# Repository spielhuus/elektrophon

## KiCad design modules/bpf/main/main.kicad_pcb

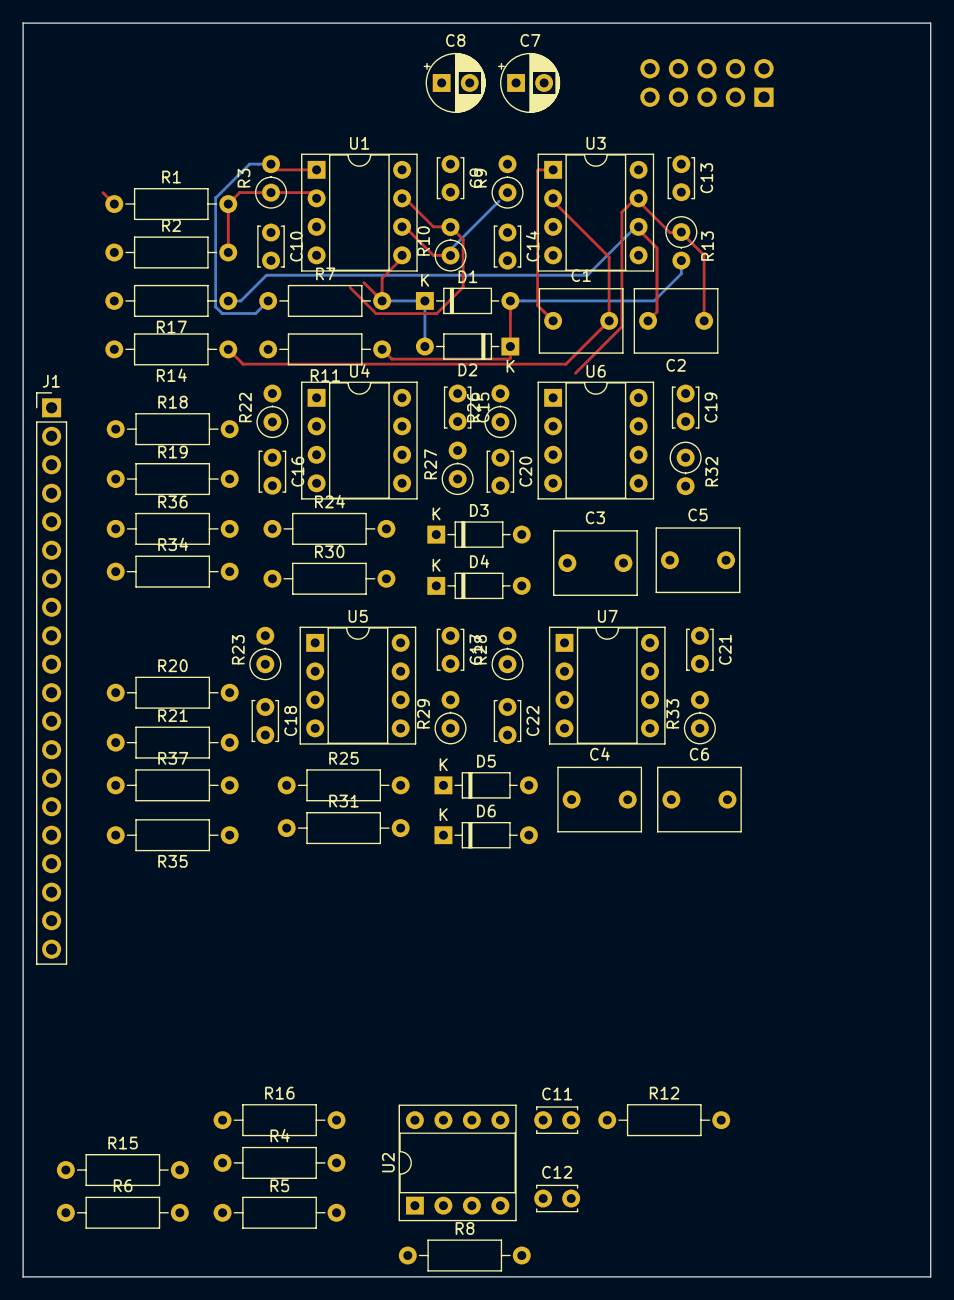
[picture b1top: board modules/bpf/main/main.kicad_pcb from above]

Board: 2 copper layers, 80.9 x 111.8 mm, 74 parts (1 on the bottom side), 49 nets.

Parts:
C1, C2, C3, C4, C5, C6: 22n; C_Rect_L7.2mm_W5.5mm_P5.00mm_FKS2_FKP2_MKS2_MKP2
C7, C8: 10u; CP_Radial_D5.0mm_P2.50mm
C9, C10, C11, C12, C13, C14, C15, C16, C17, C18, C19, C20, C21, C22: 0.1u; C_Disc_D3.4mm_W2.1mm_P2.50mm
D1, D2, D3, D4, D5, D6: 1N4148; D_DO-35_SOD27_P7.62mm_Horizontal
J1: Conn_01x20_Female; PinHeader_1x20_P2.54mm_Vertical
J2: IDC Header; IDC-Header_2x05_P2.54mm_Vertical
R1, R2, R18, R19, R20, R21: 47k; R_Axial_DIN0207_L6.3mm_D2.5mm_P10.16mm_Horizontal
R3, R22, R23: 47k; R_Axial_DIN0207_L6.3mm_D2.5mm_P2.54mm_Vertical
R4, R5, R6, R8, R12, R15, R16: 100k; R_Axial_DIN0207_L6.3mm_D2.5mm_P10.16mm_Horizontal
R7, R24, R25: 10k; R_Axial_DIN0207_L6.3mm_D2.5mm_P10.16mm_Horizontal
R9, R10, R26, R27, R28, R29: 10k; R_Axial_DIN0207_L6.3mm_D2.5mm_P2.54mm_Vertical
R11, R30, R31: 15k; R_Axial_DIN0207_L6.3mm_D2.5mm_P10.16mm_Horizontal
R13, R32, R33: 6k8; R_Axial_DIN0207_L6.3mm_D2.5mm_P2.54mm_Vertical
R14, R17, R34, R35, R36, R37: 680; R_Axial_DIN0207_L6.3mm_D2.5mm_P10.16mm_Horizontal
U1, U2, U3, U4, U5, U6, U7: TL072; DIP-8_W7.62mm_Socket

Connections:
+5V: J2.9, J2.10
+15V: C7.1, C9.1, C11.1, C13.1, C15.1, C17.1, C19.1, C21.1, J2.3, J2.4, U1.8, U2.8, U3.8, U4.8, U5.8, U6.8, U7.8
-15V: C8.2, C10.2, C12.2, C14.2, C16.2, C18.2, C20.2, C22.2, J2.1, J2.2, U1.4, U2.4, U3.4, U4.4, U5.4, U6.4, U7.4
FREQ_1_a: J1.4, R10.2, U1.7
FREQ_1_b: J1.5, R17.2
FREQ_1_c: J1.6, R14.2
FREQ_2_a: J1.10, R27.2, U4.7
FREQ_2_b: J1.11, R36.2
FREQ_2_c: J1.12, R34.2
FREQ_3_a: J1.16, R29.2, U5.7
FREQ_3_b: J1.17, R37.2
FREQ_3_c: J1.18, R35.2
GND: C7.2, C8.1, C9.2, C10.1, C11.2, C12.1, C13.2, C14.1, C15.2, C16.1, C17.2, C18.1, C19.2, C20.1, C21.2, C22.1, J2.5, J2.6, J2.7, J2.8, R11.2, R30.2, R31.2, U1.3, U2.3, U2.5, U3.3, U3.5, U4.3, U5.3, U6.3, U6.5, U7.3, U7.5
IN: J1.1, R1.1, R18.1, R20.1
IN_1: J1.2, R2.1
IN_2: J1.8, R19.1
IN_3: J1.14, R21.1
unnamed: C1.1, R9.2, U3.1
unnamed: C1.2, R14.1, U3.2
unnamed: C2.2, R17.1, U3.6
unnamed: C3.1, R26.2, U6.1
unnamed: C3.2, R34.1, U6.2
unnamed: C4.1, R28.2, U7.1
unnamed: C4.2, R35.1, U7.2
unnamed: C5.2, R36.1, U6.6
unnamed: C6.2, R37.1, U7.6
unnamed: D1.2, D2.1, R11.1, R13.2
unnamed: D3.2, D4.1, R30.1, R32.2
unnamed: D5.2, D6.1, R31.1, R33.2
unnamed: R1.2, R2.2, R3.1, U1.2
unnamed: R3.2, R7.1, U1.1
unnamed: R4.1, R5.1, R6.1, R8.2, U2.2
unnamed: R9.1, R10.1, U1.6
unnamed: R12.1, R15.2, U2.6
unnamed: R8.1, R12.2, U2.1
unnamed: R16.2, U2.7
unnamed: R18.2, R19.2, R22.1, U4.2
unnamed: R20.2, R21.2, R23.1, U5.2
unnamed: R22.2, R24.1, U4.1
unnamed: R23.2, R25.1, U5.1
unnamed: R26.1, R27.1, U4.6
unnamed: R28.1, R29.1, U5.6
OUT: J1.20, R15.1, R16.1
OUT_1: C2.1, J1.7, R13.1, U3.7
OUT_2: C5.1, J1.13, R32.1, U6.7
OUT_3: C6.1, J1.19, R33.1, U7.7
RES_1: D1.1, D2.2, J1.3, R7.2, U1.5
RES_2: D3.1, D4.2, J1.9, R24.2, U4.5
RES_3: D5.1, D6.2, J1.15, R25.2, U5.5

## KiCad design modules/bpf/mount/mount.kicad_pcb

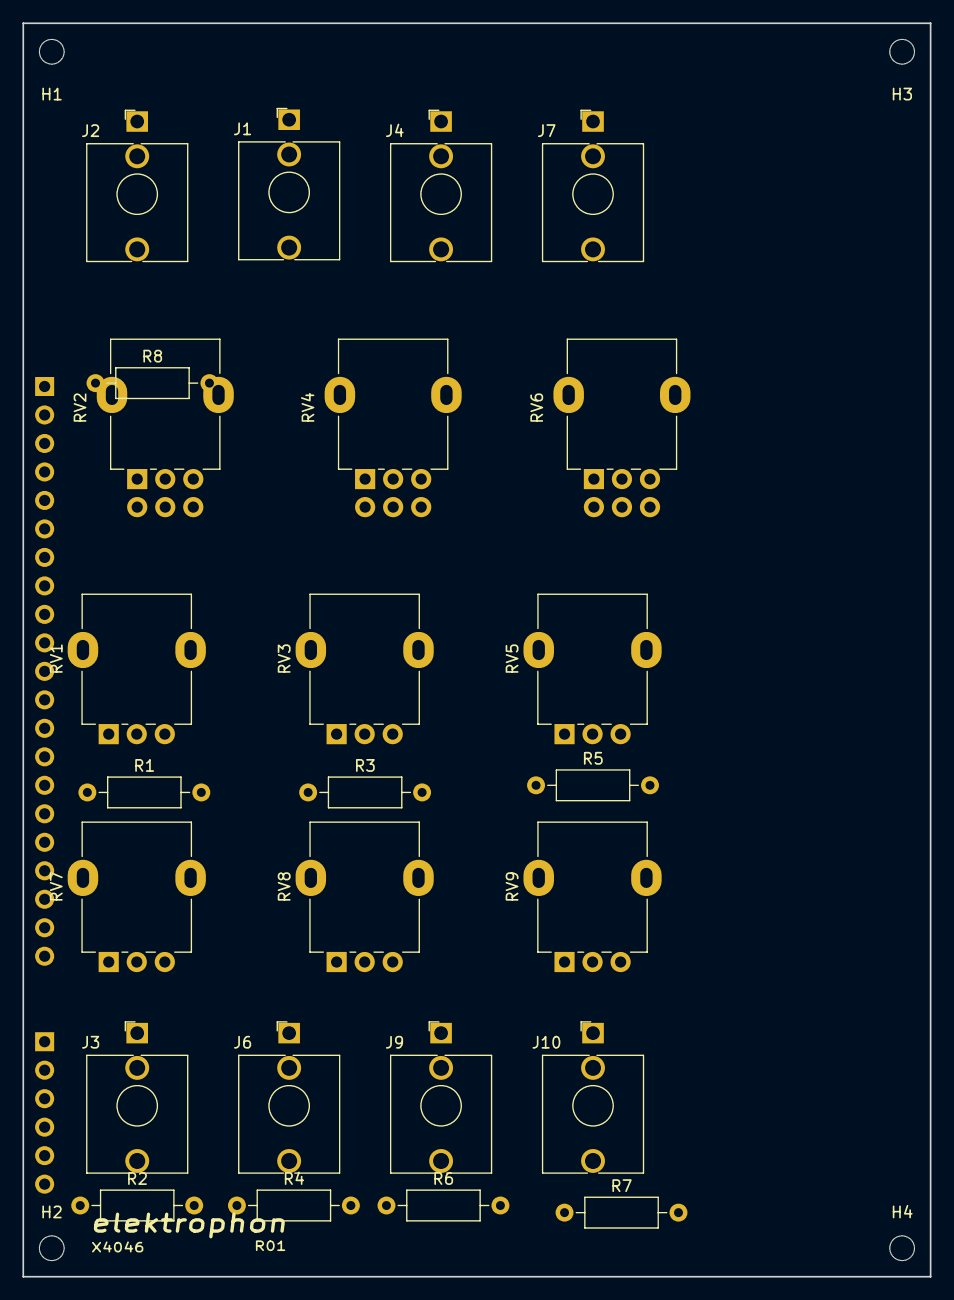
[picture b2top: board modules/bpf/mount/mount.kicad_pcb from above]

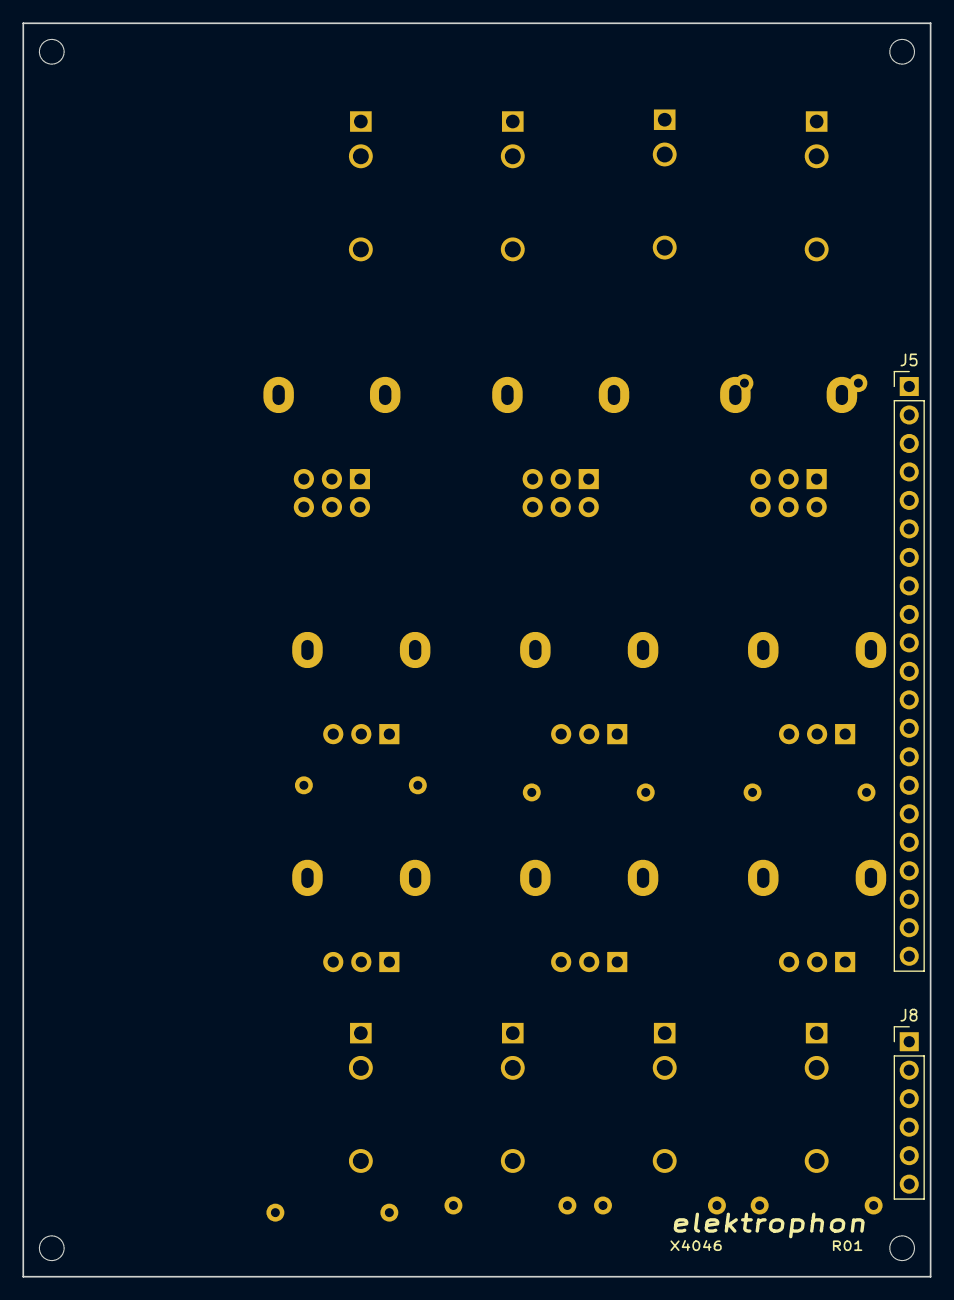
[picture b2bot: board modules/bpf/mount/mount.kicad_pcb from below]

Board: 2 copper layers, 80.9 x 111.8 mm, 31 parts (2 on the bottom side), 35 nets, no tracks yet.

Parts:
H1, H2, H3, H4: MountingHole; MountingHole_2.2mm_M2
J1, J2, J3, J4, J6, J7, J9, J10: AudioJack2_SwitchT; Jack_3.5mm_WQP-PJ398SM_Vertical
J5: Conn_01x21_Male; PinHeader_1x21_P2.54mm_Vertical
J8: Conn_01x06_Male; PinHeader_1x06_P2.54mm_Vertical
R1, R3, R5: 4k7; R_Axial_DIN0207_L6.3mm_D2.5mm_P10.16mm_Horizontal
R2, R4, R6, R7: 1k; R_Axial_DIN0207_L6.3mm_D2.5mm_P10.16mm_Horizontal
R8: 22k; R_Axial_DIN0207_L6.3mm_D2.5mm_P10.16mm_Horizontal
RV1, RV3, RV5: 50k; Potentiometer_Alpha_RD901F-40-00D_Single_Vertical
RV2, RV4, RV6: 100k; Potentiometer_Alpha_RD902F-40-00D_Dual_Vertical
RV7, RV8, RV9: 100k; Potentiometer_Alpha_RD901F-40-00D_Single_Vertical

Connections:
FREQ_1_a: J5.5, RV2.1
FREQ_1_b: J5.6, RV2.2, RV2.3
FREQ_1_c: J5.7, RV2.4
FREQ_2_a: J5.11, RV4.1
FREQ_2_b: J5.12, RV4.2, RV4.3
FREQ_2_c: J5.13, RV4.4
FREQ_3_a: J5.17, RV6.1
FREQ_3_b: J5.18, RV6.2, RV6.3
FREQ_3_c: J5.19, RV6.4
GND: J1.S, J2.S, J3.S, J4.S, J5.1, J6.S, J7.S, J9.S, J10.S, R1.2, R3.2, R5.2, RV7.1, RV8.1, RV9.1
IN: J2.T, J5.2
IN_1: J1.T, J5.3
IN_2: J4.T, J5.9
IN_3: J5.15, J7.T
MIX_1_a: J8.1, RV7.3
MIX_1_b: J8.2, RV7.2
MIX_2_a: J8.3, RV8.3
MIX_2_b: J8.4, RV8.2
MIX_3_a: J8.5, RV9.3
MIX_3_b: J8.6, RV9.2
unnamed: J3.T, R2.2
unnamed: J6.T, R4.2
unnamed: J9.T, R6.2
unnamed: J10.T, R7.2
unnamed: R1.1, RV1.1
unnamed: R3.1, RV3.1
unnamed: R5.1, RV5.1
unnamed: R8.1, RV1.3
OUT: J5.21, R7.1
OUT_1: J5.8, R2.1, R8.2, RV2.5, RV2.6
OUT_2: J5.14, R4.1, RV3.3, RV4.5, RV4.6
OUT_3: J5.20, R6.1, RV5.3, RV6.5, RV6.6
RES_1: J5.4, RV1.2
RES_2: J5.10, RV3.2
RES_3: J5.16, RV5.2

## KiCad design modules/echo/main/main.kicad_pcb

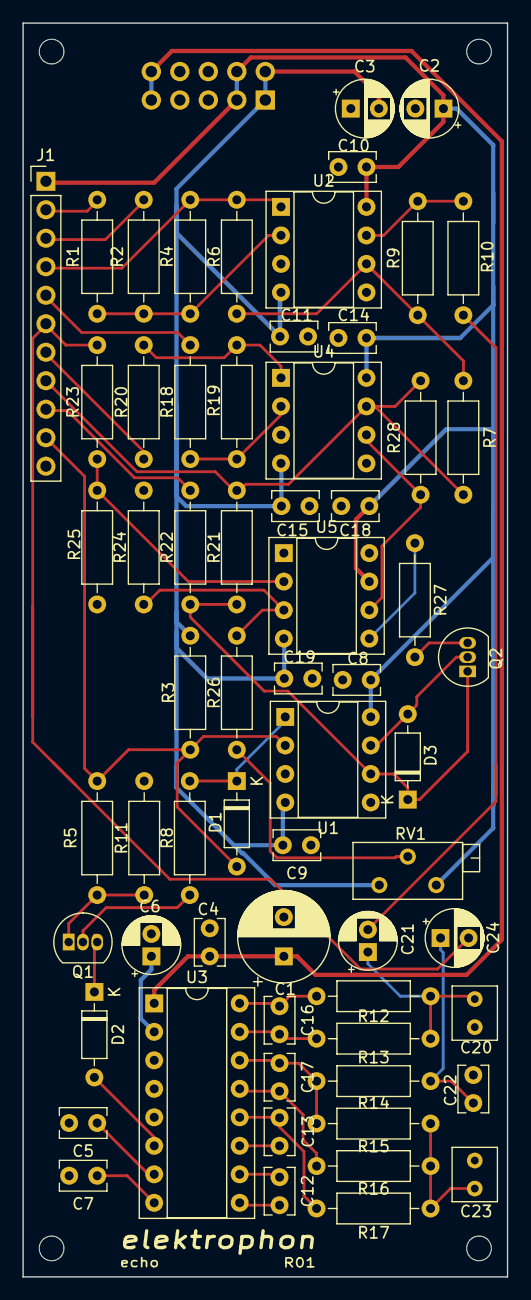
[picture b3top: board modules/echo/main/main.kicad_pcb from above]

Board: 2 copper layers, 43.2 x 111.8 mm, 69 parts (1 on the bottom side), 46 nets.

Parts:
C1: 100u; CP_Radial_D8.0mm_P3.50mm
C2, C3, C24: 10u; CP_Radial_D5.0mm_P2.50mm
C4, C5, C7, C8, C9, C10, C11, C12, C13, C14, C15, C18, C19: 0.1u; C_Rect_L4.0mm_W2.5mm_P2.50mm
C6, C21: 4.7u; CP_Radial_D5.0mm_P2.00mm
C16, C17: 560p; C_Rect_L4.0mm_W2.5mm_P2.50mm
C20, C23: 5n6; C_Rect_L4.6mm_W3.8mm_P2.50mm_MKS02_FKP02
C22: 10n; C_Rect_L4.0mm_W2.5mm_P2.50mm
D1, D2, D3: 1N4148; D_DO-35_SOD27_P7.62mm_Horizontal
H1, H2, H3, H4: MountingHole; MountingHole_2.2mm_M2
J1: Conn_01x11_Female; PinHeader_1x11_P2.54mm_Vertical
J2: IDC Header; IDC-Header_2x05_P2.54mm_Vertical
Q1: 2N3904; TO-92_Inline
Q2: 2N3906; TO-92_Inline
R1, R2, R4, R6, R7, R9, R18, R19, R23: 100k; R_Axial_DIN0207_L6.3mm_D2.5mm_P10.16mm_Horizontal
R3: 300k; R_Axial_DIN0207_L6.3mm_D2.5mm_P10.16mm_Horizontal
R5, R27: 27k; R_Axial_DIN0207_L6.3mm_D2.5mm_P10.16mm_Horizontal
R8: 220k; R_Axial_DIN0207_L6.3mm_D2.5mm_P10.16mm_Horizontal
R10, R13, R15, R17: 15k; R_Axial_DIN0207_L6.3mm_D2.5mm_P10.16mm_Horizontal
R11, R24, R25: 470; R_Axial_DIN0207_L6.3mm_D2.5mm_P10.16mm_Horizontal
R12, R16: 10k; R_Axial_DIN0207_L6.3mm_D2.5mm_P10.16mm_Horizontal
R14: 2k7; R_Axial_DIN0207_L6.3mm_D2.5mm_P10.16mm_Horizontal
R20: 1k; R_Axial_DIN0207_L6.3mm_D2.5mm_P10.16mm_Horizontal
R21: 20k; R_Axial_DIN0207_L6.3mm_D2.5mm_P10.16mm_Horizontal
R22, R28: 47k; R_Axial_DIN0207_L6.3mm_D2.5mm_P10.16mm_Horizontal
R26: 1M; R_Axial_DIN0207_L6.3mm_D2.5mm_P10.16mm_Horizontal
RV1: 100k; Potentiometer_Bourns_3296Z_Horizontal
U1: TL072; DIP-8_W7.62mm_Socket
U2, U4: OPA2134; DIP-8_W7.62mm_Socket
U3: PT2399; DIP-16_W7.62mm_Socket
U5: CA3080; DIP-8_W7.62mm_Socket

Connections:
+5V: C1.1, C4.1, J2.9, J2.10, U3.1
+15V: C2.1, C8.1, C10.1, C14.1, C18.1, J1.1, J2.3, J2.4, RV1.3, U1.8, U2.8, U4.8, U5.7
-15V: C3.2, C9.2, C11.2, C15.2, C19.2, J2.1, J2.2, R3.1, RV1.1, U1.4, U2.4, U4.4, U5.4
/CV: D1.2, J1.10, R3.2, R5.2, U1.2
/IN1: J1.2, R1.2
/IN2: J1.3, R2.2
/MIXED_OUT: J1.7, R20.1
/MIX_1: J1.4, R4.1, R6.2, U2.1
/MIX_2: J1.5, R18.2
/MIX_3: C24.2, J1.6, R23.2
/RECIRC: J1.8, R7.2, R21.2, R28.2, U4.7
/RECIRC_ATTEN: J1.9, R22.2
/VCO: D2.2, U3.6
GND: C1.2, C2.2, C3.1, C4.2, C5.2, C6.2, C7.2, C8.2, C9.1, C10.2, C11.1, C14.2, C15.1, C18.2, C19.1, C20.2, C22.2, C23.2, J1.11, J2.5, J2.6, J2.7, J2.8, R11.1, R24.2, R25.2, U1.3, U1.5, U2.3, U2.5, U3.3, U3.4, U4.3, U4.5
unnamed: C5.1, U3.7
unnamed: C6.1, U3.2
unnamed: C7.1, U3.8
unnamed: C12.1, U3.10
unnamed: C12.2, U3.9
unnamed: C13.1, U3.11
unnamed: C13.2, R17.2, U3.12
unnamed: C16.1, R12.2, U3.16
unnamed: C16.2, R13.2, U3.15
unnamed: C17.1, R14.2, R15.2, U3.14
unnamed: C17.2, R16.2, U3.13
unnamed: C20.1, C21.1, R12.1, R13.1
unnamed: C21.2, R10.1
unnamed: C22.1, C24.1, R14.1
unnamed: C23.1, R15.1, R16.1, R17.1
unnamed: D1.1, R8.2, U1.1
unnamed: D2.1, Q1.3
unnamed: D3.1, Q2.1, R21.1, R22.1, U1.6
unnamed: D3.2, Q2.2, U1.7
unnamed: Q1.1, R5.1, R11.2
unnamed: Q1.2, R8.1
unnamed: Q2.3, R27.1
unnamed: R1.1, R2.1, R4.2, U2.2
unnamed: R6.1, R7.1, R9.2, U2.6
unnamed: R9.1, R10.2, U2.7
unnamed: R18.1, R19.2, U4.2
unnamed: R19.1, R20.2, U4.1
unnamed: R23.1, R25.1, U5.2
unnamed: R24.1, R26.2, U5.3
unnamed: R26.1, RV1.2
unnamed: R27.2, U5.5
unnamed: R28.1, U4.6, U5.6

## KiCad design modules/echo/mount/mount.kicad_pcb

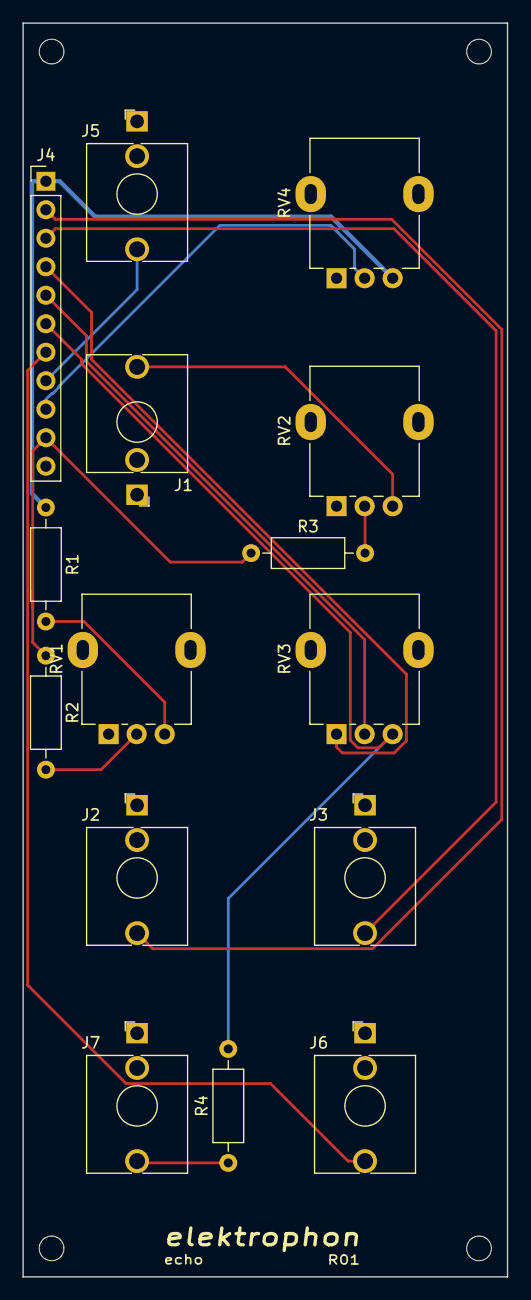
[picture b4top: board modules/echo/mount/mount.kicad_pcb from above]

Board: 2 copper layers, 43.2 x 111.8 mm, 19 parts (0 on the bottom side), 16 nets.

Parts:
H1, H2, H3, H4: MountingHole; MountingHole_2.2mm_M2
J1: CV; Jack_3.5mm_WQP-PJ398SM_Vertical
J2, J3: IN; Jack_3.5mm_WQP-PJ398SM_Vertical
J4: Conn_01x11_Male; PinHeader_1x11_P2.54mm_Vertical
J5: RECIRC; Jack_3.5mm_WQP-PJ398SM_Vertical
J6: Mixed OUT; Jack_3.5mm_WQP-PJ398SM_Vertical
J7: delayed OUT; Jack_3.5mm_WQP-PJ398SM_Vertical
R1: 360; R_Axial_DIN0207_L6.3mm_D2.5mm_P10.16mm_Horizontal
R2: 300k; R_Axial_DIN0207_L6.3mm_D2.5mm_P10.16mm_Horizontal
R3: 100k; R_Axial_DIN0207_L6.3mm_D2.5mm_P10.16mm_Horizontal
R4: 1k; R_Axial_DIN0207_L6.3mm_D2.5mm_P10.16mm_Horizontal
RV1: 100k; Potentiometer_Alpha_RD901F-40-00D_Single_Vertical
RV2, RV4: 10k; Potentiometer_Alpha_RD901F-40-00D_Single_Vertical
RV3: 10k LIN; Potentiometer_Alpha_RD901F-40-00D_Single_Vertical

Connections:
+15V: J4.1, R1.1, RV4.3
/CV: J4.10, R2.1, R3.1
/IN1: J2.T, J4.2
/IN2: J3.T, J4.3
/MIXED_OUT: J4.7, J6.T
/MIX_1: J4.4, RV3.1
/MIX_2: J4.5, RV3.2
/MIX_3: J4.6, R4.2, RV3.3
/RECIRC_ATTEN: J4.9, RV4.2
/RECIRC_CV: J4.8, J5.T
GND: J1.S, J2.S, J3.S, J4.11, J5.S, J6.S, J7.S, RV1.1, RV2.1, RV4.1
unnamed: J1.T, RV2.3
unnamed: J7.T, R4.1
unnamed: R1.2, RV1.3
unnamed: R2.2, RV1.2
unnamed: R3.2, RV2.2

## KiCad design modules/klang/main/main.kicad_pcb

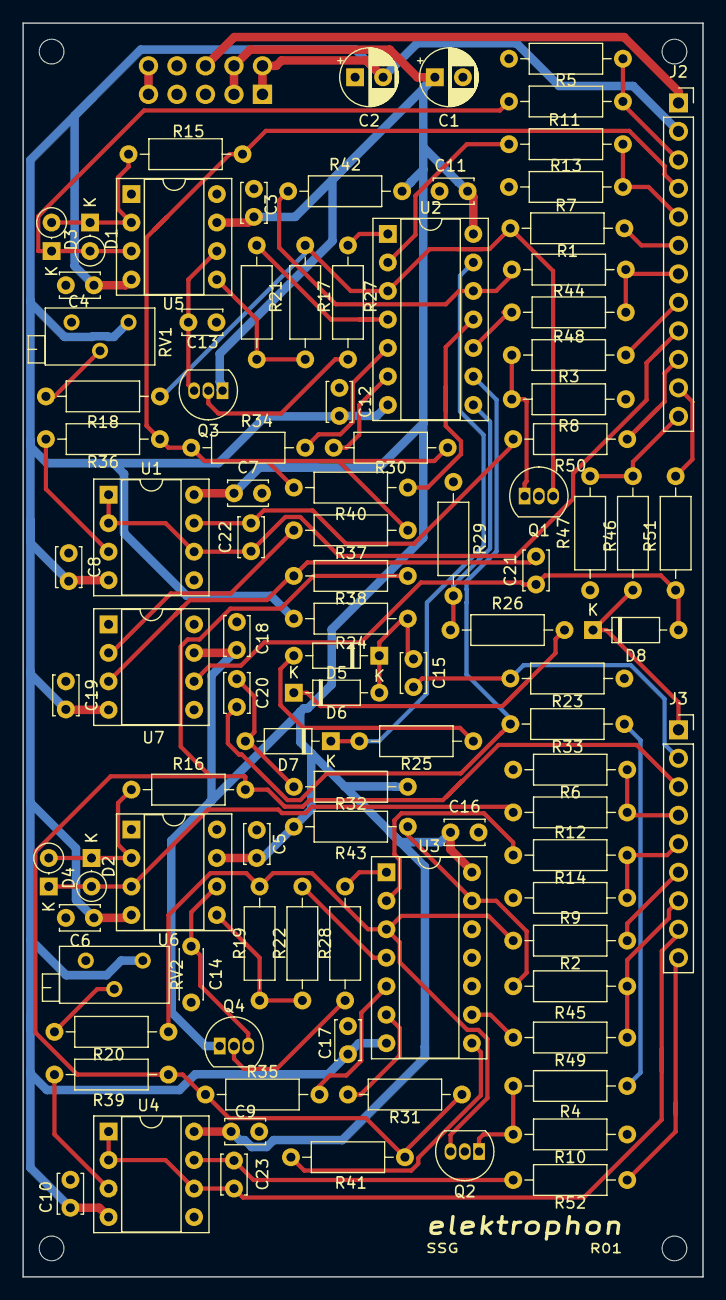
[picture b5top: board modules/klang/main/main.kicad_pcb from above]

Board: 2 copper layers, 60.6 x 111.8 mm, 99 parts (1 on the bottom side), 70 nets.

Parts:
C1, C2: 10u; CP_Radial_D5.0mm_P2.50mm
C3, C4, C5, C6, C7, C8, C9, C10, C11, C12, C16, C17, C18, C19: 0.1u; C_Disc_D3.4mm_W2.1mm_P2.50mm
C13: 100n; C_Disc_D3.4mm_W2.1mm_P2.50mm
C14: 220n; C_Disc_D4.3mm_W1.9mm_P5.00mm
C15, C20: 1n; C_Disc_D3.4mm_W2.1mm_P2.50mm
C21: 100p; C_Disc_D3.4mm_W2.1mm_P2.50mm
C22, C23: 47p; C_Disc_D3.4mm_W2.1mm_P2.50mm
D1, D2, D3, D4: 1N4148; D_DO-35_SOD27_P2.54mm_Vertical_KathodeUp
D5, D6, D7, D8: 1N4148; D_DO-35_SOD27_P7.62mm_Horizontal
J1: IDC Header; IDC-Header_2x05_P2.54mm_Vertical
J2: Conn_01x12_Female; PinSocket_1x12_P2.54mm_Vertical
J3: Conn_01x09_Female; PinSocket_1x09_P2.54mm_Vertical
Q1, Q2: PN4250; TO-92_Inline
Q3, Q4: 2N5457; TO-92_Inline
R1, R2, R13, R14: 2M7; R_Axial_DIN0207_L6.3mm_D2.5mm_P10.16mm_Horizontal
R3, R4, R5, R6, R11, R12, R15, R16, R24: 33k; R_Axial_DIN0207_L6.3mm_D2.5mm_P10.16mm_Horizontal
R7, R9, R23, R26: 100k; R_Axial_DIN0207_L6.3mm_D2.5mm_P10.16mm_Horizontal
R8, R10, R21, R22: 15k; R_Axial_DIN0207_L6.3mm_D2.5mm_P10.16mm_Horizontal
R17, R19: 82k; R_Axial_DIN0207_L6.3mm_D2.5mm_P10.16mm_Horizontal
R18, R20, R32: 1M5; R_Axial_DIN0207_L6.3mm_D2.5mm_P10.16mm_Horizontal
R25: 680k; R_Axial_DIN0207_L6.3mm_D2.5mm_P10.16mm_Horizontal
R27, R31: 820k; R_Axial_DIN0207_L6.3mm_D2.5mm_P10.16mm_Horizontal
R28: 1m; R_Axial_DIN0207_L6.3mm_D2.5mm_P10.16mm_Horizontal
R29: 4M7; R_Axial_DIN0207_L6.3mm_D2.5mm_P10.16mm_Horizontal
R30, R42, R43: 1M; R_Axial_DIN0207_L6.3mm_D2.5mm_P10.16mm_Horizontal
R33, R34, R35: 330; R_Axial_DIN0207_L6.3mm_D2.5mm_P10.16mm_Horizontal
R36, R37, R38, R39: 10k; R_Axial_DIN0207_L6.3mm_D2.5mm_P10.16mm_Horizontal
R40, R41: 470k; R_Axial_DIN0207_L6.3mm_D2.5mm_P10.16mm_Horizontal
R44, R45: 2M2; R_Axial_DIN0207_L6.3mm_D2.5mm_P10.16mm_Horizontal
R46, R47, R48, R49, R51: 3k3; R_Axial_DIN0207_L6.3mm_D2.5mm_P10.16mm_Horizontal
R50, R52: 100; R_Axial_DIN0207_L6.3mm_D2.5mm_P10.16mm_Horizontal
RV1, RV2: 25k; Potentiometer_Bourns_3296Z_Horizontal
U1, U4: TL072; DIP-8_W7.62mm_Socket
U2, U3: LM3900; DIP-14_W7.62mm_Socket
U5, U6: CA3080; DIP-8_W7.62mm_Socket
U7: LM741; DIP-8_W7.62mm_Socket

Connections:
+5V: J1.9, J1.10
+15V: C1.1, C3.1, C5.1, C7.1, C9.1, C11.1, C16.1, C18.1, J1.3, J1.4, Q3.1, Q4.1, R32.2, R42.2, R43.2, U1.8, U2.14, U3.14, U4.8, U5.7, U6.7, U7.7
-15V: C2.2, C4.2, C6.2, C8.2, C10.2, C12.2, C17.2, C19.2, J1.1, J1.2, J2.2, R24.1, RV1.1, RV2.1, U1.4, U2.7, U3.7, U4.4, U5.4, U6.4, U7.4
/HOLD: R4.2, R33.1
COUPLER_5V: J2.12, R46.1, R47.2
COUPLER_HOT: J2.11, R51.1
CYCLE_1: J2.7, R44.1, R48.1
CYCLE_2: J3.7, R45.1, R49.1
GND: C1.2, C2.1, C3.2, C4.1, C5.2, C6.1, C7.2, C8.1, C9.2, C10.1, C11.2, C12.1, C13.2, C14.2, C16.2, C17.1, C18.2, C19.1, J1.5, J1.6, J1.7, J1.8, J2.1, Q1.2, Q2.2, R5.1, R6.1, R7.1, R8.1, R9.1, R10.1, R23.1, R29.1, R47.1, RV1.3, RV2.3, U1.5, U4.5
HOLD_1: J2.8, R3.2
IN_1: J2.3, R5.2, R11.2
IN_2: J3.4, R6.2, R12.2
LED: D8.1, J3.1, R46.2
LED_1_a: C22.1, J2.9, U1.1, U1.2, U1.6
LED_1_b: J2.10, R50.1
LED_2_a: C23.1, J3.8, U4.1, U4.2, U4.6
LED_2_b: J3.9, R52.1
unnamed: C13.1, Q3.3, U5.6
unnamed: C14.1, Q4.3, U6.6
unnamed: C15.2, D5.1, D6.2, R24.2
unnamed: C20.1, R33.2, U2.9
unnamed: C20.2, D7.2, R32.1
unnamed: C21.1, D8.2, R51.2, U7.6
unnamed: C21.2, R38.1, U7.3
unnamed: C22.2, R50.2, U1.7
unnamed: C23.2, R52.2, U4.7
unnamed: D1.1, D3.2, R15.2, U5.2
unnamed: D1.2, D3.1, R11.1, U5.3
unnamed: D2.1, D4.2, R16.2, U6.2
unnamed: D2.2, D4.1, R12.1, U6.3
unnamed: D5.2, R25.2
unnamed: D6.1, R26.2
unnamed: D7.1, R25.1, U2.13
unnamed: Q1.1, R3.1, R8.2
unnamed: Q1.3, R1.1, R17.2, R18.2, U2.3
unnamed: Q2.1, R4.1, R10.2
unnamed: Q2.3, R2.1, R19.2, R20.2, U3.3
unnamed: Q3.2, R27.2
unnamed: Q4.2, R28.2
unnamed: R13.1, U2.2
unnamed: R14.1, U3.2
unnamed: R17.1, R21.1, U5.5
unnamed: R18.1, RV1.2
unnamed: R19.1, R22.1, U6.5
unnamed: R20.1, RV2.2
unnamed: R21.2, U2.4
unnamed: R22.2, U3.4
unnamed: R26.1, R29.2, U2.8
unnamed: R27.1, U2.1
unnamed: R28.1, U3.1
unnamed: R30.1, U2.6
unnamed: R31.1, U3.6
unnamed: R34.2, U2.5
unnamed: R35.2, U3.5
unnamed: R36.1, U1.3
unnamed: R37.1, U7.2
unnamed: R39.1, U4.3
unnamed: R40.1, U2.11
unnamed: R41.1, U3.8
unnamed: R42.1, R44.2, U2.12
unnamed: R43.1, R45.2, U3.13
unnamed: R48.2, U2.10
unnamed: R49.2, U3.9
OUT_1: J2.4, R15.1, R30.2, R34.1, R36.2, R37.2, R40.2
OUT_2: J3.3, R16.1, R31.2, R35.1, R38.2, R39.2, R41.2
RATE_1: J2.6, R1.2
RATE_2: J3.6, R2.2
SAMPLE_2: C15.1, J3.2, R23.2
VC_1: J2.5, R7.2, R13.2
VC_2: J3.5, R9.2, R14.2

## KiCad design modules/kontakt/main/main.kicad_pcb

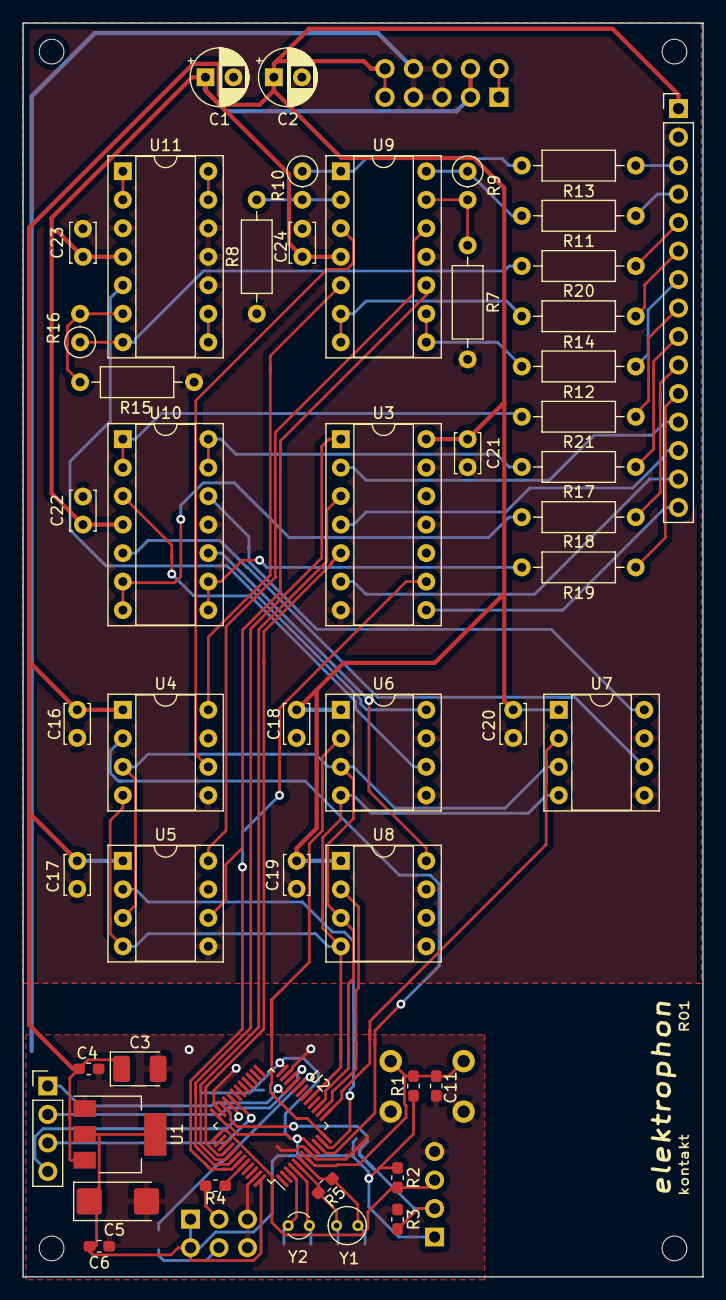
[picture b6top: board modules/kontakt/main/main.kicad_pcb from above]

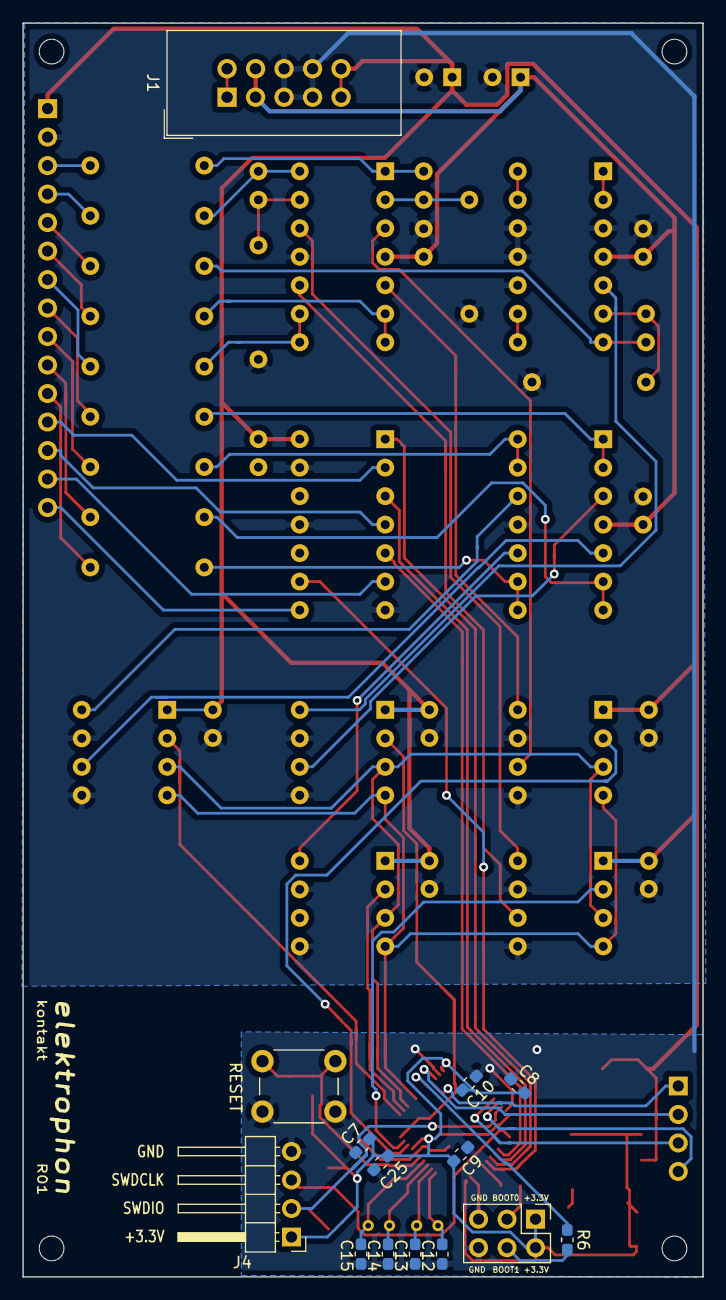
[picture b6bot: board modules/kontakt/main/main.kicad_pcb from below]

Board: 2 copper layers, 60.6 x 111.8 mm, 69 parts (14 on the bottom side), 68 nets.

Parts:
C1, C2: 10u; CP_Radial_D5.0mm_P2.50mm
C3: 100u; CP_EIA-3528-15_AVX-H_Pad1.50x2.35mm_HandSolder
C4, C6, C8, C9, C10, C11: 100n; C_0603_1608Metric_Pad1.05x0.95mm_HandSolder
C5: 330u; CP_EIA-6032-20_AVX-F_Pad2.25x2.35mm_HandSolder
C7: 10n; C_0603_1608Metric_Pad1.05x0.95mm_HandSolder
C12, C13, C14, C15: 20p; C_0603_1608Metric_Pad1.05x0.95mm_HandSolder
C16, C17, C18, C19, C20, C21, C22, C23, C24: 0.1u; C_Disc_D3.4mm_W2.1mm_P2.50mm
C25: 1u; C_0603_1608Metric_Pad1.05x0.95mm_HandSolder
H1, H2, H3, H4: MountingHole; MountingHole_2.2mm_M2
J1: IDC Header; IDC-Header_2x05_P2.54mm_Vertical
J2: Conn_01x15_Female; PinHeader_1x15_P2.54mm_Vertical
J3: Conn_01x04_Female; PinHeader_1x04_P2.54mm_Vertical
J4: SWD; PinHeader_1x04_P2.54mm_Horizontal
J5: Conn_02x03_Odd_Even; PinHeader_2x03_P2.54mm_Vertical
R1, R2, R3: 10k; R_0603_1608Metric_Pad1.05x0.95mm_HandSolder
R4, R6: 100k; R_0603_1608Metric_Pad1.05x0.95mm_HandSolder
R5: 1M; R_0603_1608Metric_Pad1.05x0.95mm_HandSolder
R7, R8, R15: 22k; R_Axial_DIN0207_L6.3mm_D2.5mm_P10.16mm_Horizontal
R9, R10, R16: 17k; R_Axial_DIN0207_L6.3mm_D2.5mm_P2.54mm_Vertical
R11, R12, R13, R14, R17, R18, R19, R20, R21: 1k; R_Axial_DIN0207_L6.3mm_D2.5mm_P10.16mm_Horizontal
RESET: SW_Push; SW_PUSH_6mm
U1: AMS1117-3.3; SOT-223-3_TabPin2
U2: STM32F103C8Tx; LQFP-48_7x7mm_P0.5mm
U3: 40106; DIP-14_W7.62mm_Socket
U4, U5, U6, U7, U8: MCP4822; DIP-8_W7.62mm_Socket
U9, U10, U11: LM324; DIP-14_W7.62mm_Socket
Y1: 8MHz; Crystal_Round_D3.0mm_Vertical
Y2: 32.768K; Crystal_Round_D2.0mm_Vertical

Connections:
+3V3: C5.1, C6.2, C7.2, C8.2, C9.2, C10.2, C25.2, J4.1, J5.1, J5.2, R1.2, R2.1, U1.2, U2.9, U2.24, U2.36, U2.48
+5V: C2.1, C3.1, C4.2, C16.1, C17.1, C18.1, C19.1, C20.1, C21.1, J1.9, J1.10, J2.1, U1.3, U3.14, U4.1, U5.1, U6.1, U7.1, U8.1
+15V: C1.1, C22.1, C23.1, C24.1, J1.3, J1.4, U9.4, U10.4, U11.4
-15V: J1.1, J1.2
/Analog Circuit/SIG_NOTE_1: U4.6, U9.3
/Analog Circuit/SIG_NOTE_2: U5.8, U9.12
/Analog Circuit/SIG_NOTE_3: U6.8, U11.5
/Analog Circuit/SIG_PITCH_BEND_1: U7.8, U10.12
/Analog Circuit/SIG_PITCH_BEND_2: U7.6, U10.5
/Analog Circuit/SIG_PITCH_BEND_3: U8.8, U10.10
/Analog Circuit/SIG_VELOCITY_1: U4.8, U9.5
/Analog Circuit/SIG_VELOCITY_2: U5.6, U9.10
/Analog Circuit/SIG_VELOCITY_3: U6.6, U10.3
/STM32 Board/BOOT0: R4.1, U2.44
/STM32 Board/BOOT1: R6.1, U2.20
/STM32 Board/OSCIN: C14.1, R5.1, U2.5, Y1.1
/STM32 Board/OSCOUT: C15.1, R5.2, U2.6, Y1.2
/STM32 Board/PC14: C12.1, U2.3, Y2.1
/STM32 Board/PC15: C13.1, U2.4, Y2.2
/STM32 Board/RESET: C11.2, R1.1, RESET.2, U2.7
/STM32 Board/SWDCLK: J4.3, R2.2, U2.37
/STM32 Board/SWDIO: J4.2, R3.2, U2.34
CS_1: U2.10, U4.2
CS_2: U2.11, U5.2
CS_3: U2.12, U6.2
CS_4: U2.13, U7.2
CS_5: U2.14, U8.2
GND: C1.2, C2.2, C3.2, C4.1, C5.2, C6.1, C7.1, C8.1, C9.1, C10.1, C11.1, C12.2, C13.2, C14.2, C15.2, C16.2, C17.2, C18.2, C19.2, C20.2, C21.2, C22.2, C23.2, C24.2, C25.1, J1.5, J1.6, J1.7, J1.8, J2.2, J4.4, J5.5, J5.6, R3.1, R7.1, R8.1, R15.1, RESET.1, U1.1, U2.8, U2.23, U2.35, U2.47, U3.7, U3.11, U3.13, U4.5, U4.7, U5.5, U5.7, U6.5, U6.7, U7.5, U7.7, U8.5, U8.7, U9.11, U10.11, U11.3, U11.10, U11.11, U11.12
LED_ACTIVITY: J3.1, U2.21
LED_CONNECT: J3.2, U2.22
MOSI: U2.17, U4.4, U5.4, U6.4, U7.4, U8.4
unnamed: J5.3, R4.2
unnamed: J5.4, R6.2
unnamed: R7.2, R9.2, U9.13
unnamed: R10.1, R13.2, U9.1
unnamed: R8.2, R10.2, U9.2
unnamed: R9.1, R11.2, U9.14
unnamed: R12.2, U9.8, U9.9
unnamed: R14.2, U9.6, U9.7
unnamed: R15.2, R16.2, U11.6
unnamed: R16.1, R20.2, U11.7
unnamed: R17.2, U10.13, U10.14
unnamed: R18.2, U10.6, U10.7
unnamed: R19.2, U10.8, U10.9
unnamed: R21.2, U10.1, U10.2
unnamed: U11.1, U11.2
unnamed: U11.8, U11.9
unnamed: U11.13, U11.14
Note_1: J2.3, R13.1
Note_2: J2.4, R11.1
Note_3: J2.5, R20.1
OUT_CLOCK: J2.15, U3.8
OUT_TRIGGER_1: J2.12, U3.2
OUT_TRIGGER_2: J2.13, U3.4
OUT_TRIGGER_3: J2.14, U3.6
PA11: J3.3, U2.32
PA12: J3.4, U2.33
PITCH_BEND_1: J2.9, R17.1
PITCH_BEND_2: J2.10, R18.1
PITCH_BEND_3: J2.11, R19.1
SCK: U2.15, U4.3, U5.3, U6.3, U7.3, U8.3
SIG_CLOCK: U2.43, U3.9
SIG_TRIGGER_1: U2.42, U3.1
SIG_TRIGGER_2: U2.41, U3.3
SIG_TRIGGER_3: U2.40, U3.5
Velocity_1: J2.6, R14.1
Velocity_2: J2.7, R12.1
Velocity_3: J2.8, R21.1

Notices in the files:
modules/bpf/main/main.kicad_pcb:
License CC BY 4.0 - Attribution 4.0 International
